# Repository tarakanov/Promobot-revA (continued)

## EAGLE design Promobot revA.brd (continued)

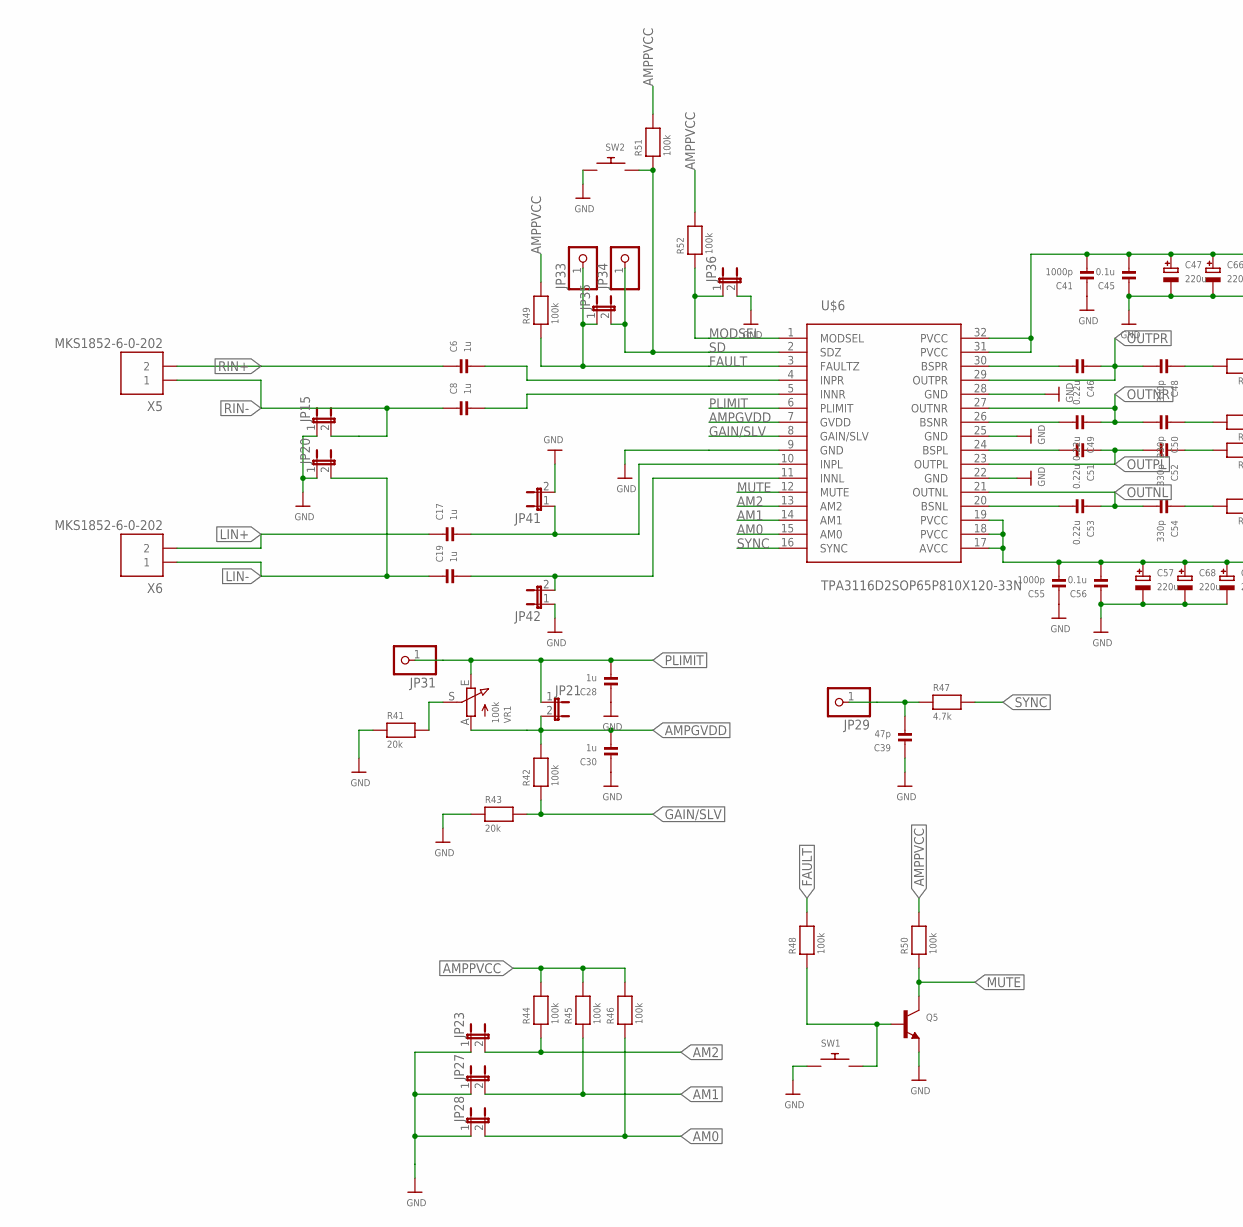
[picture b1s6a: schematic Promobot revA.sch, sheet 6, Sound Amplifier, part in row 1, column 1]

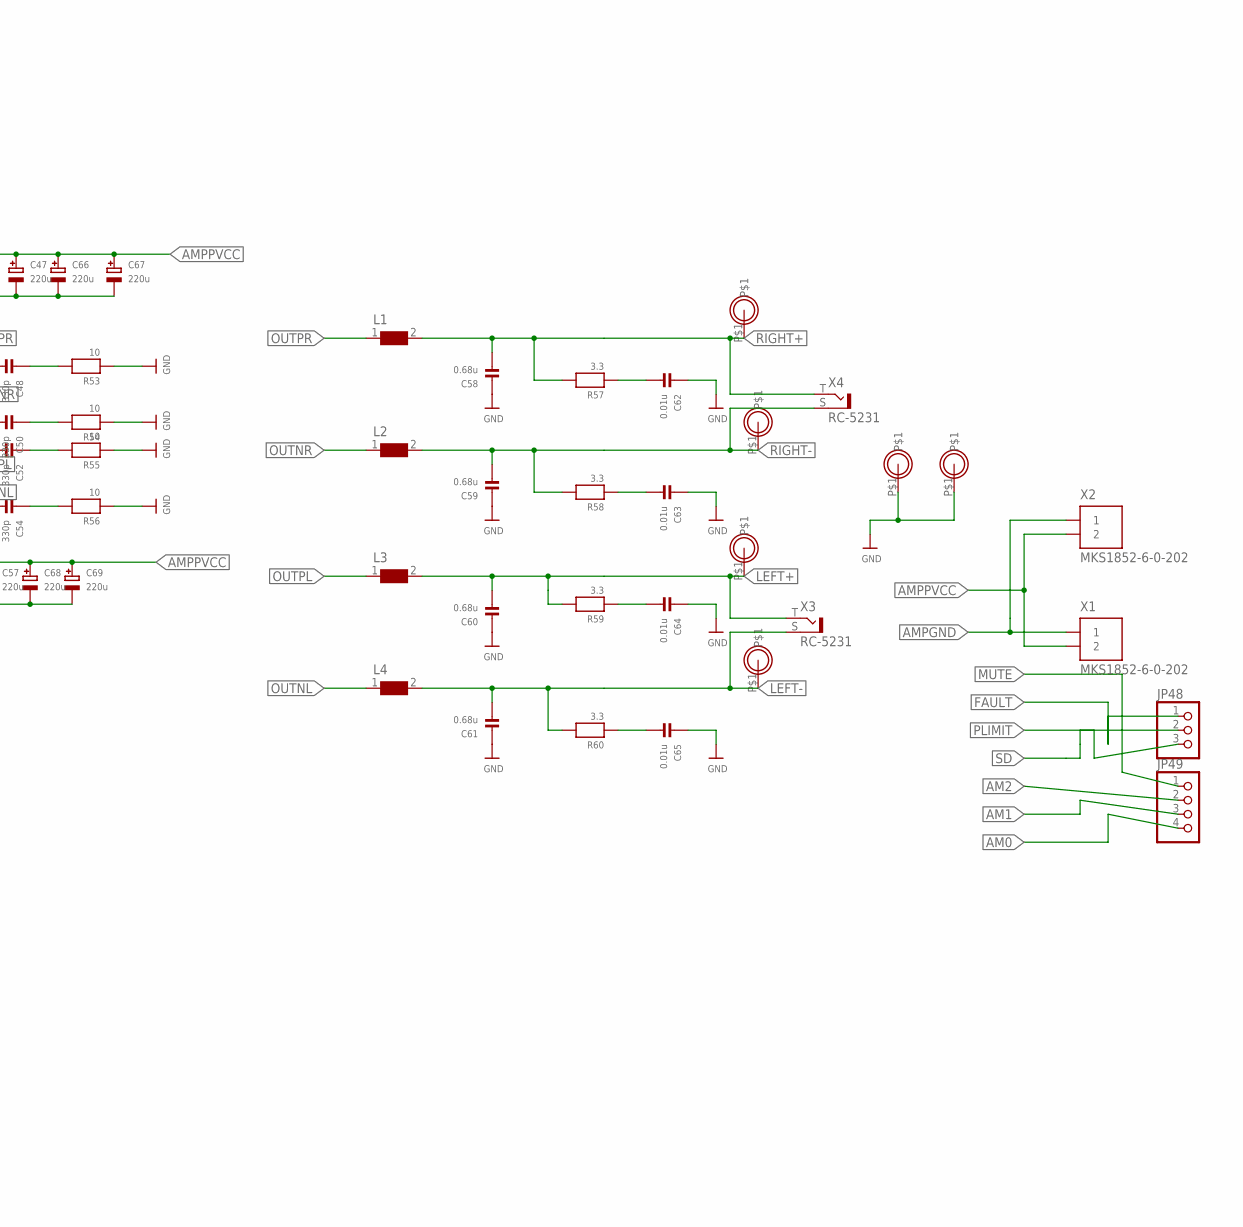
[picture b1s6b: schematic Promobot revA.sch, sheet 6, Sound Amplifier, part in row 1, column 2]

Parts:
C6, C8, C17, C19: 1u; _0603
C28, C30: 1u; _0603MP
C39: 47p; _0603
C41, C55: 1000p; _0603
C45, C56: 0.1u; _0603
C46, C49, C51, C53: 0.22u; _0603
C47, C57, C66, C67, C68, C69: 220u; CELEC_3.5MM_10MM
C48, C50, C52, C54: 330p; _0603
C58, C59, C60, C61: 0.68u; 1206
C62, C63, C64, C65: 0.01u; _0805
JP15, JP20, JP21, JP23, JP27, JP28, JP35, JP36, JP41, JP42: JUMPER2
JP29, JP31, JP33, JP34: HEADER-1X1ROUND; 1X01_ROUND
JP48: HEADER-1X376MIL; 1X03_ROUND_76
JP49: HEADER-1X476MIL; 1X04_ROUND_76
L1, L2, L3, L4: WE-PD-7447709100_1260/1245/1280/1210; WE-PD_1260/1245/1280/1210
Q5: TRANSISTOR_NPNWAVE; SOT23-W
R41: 20k; 0603
R42: 100k; _0805
R43: 20k; _0805
R44, R45, R46, R48, R49, R50, R51, R52: 100k; 0603
R47: 4.7k; 0603
R53, R54, R55, R56: 10; 1206
R57, R58, R59, R60: 3.3; _0603
SW1, SW2: SWITCH_PUSHBUTTONSOFTTOUCHSMD_SJ; PUSHBUTTON_SMD_SJ
U$6: TPA3116D2SOP65P810X120-33N; SOP65P810X120-33N
U$81, U$82, U$83, U$84, U$89, U$90: MOUNTINGHOLE; MOUNTINGHOLE_3.0_PLATED
VR1: 100k; TRIMPOT_BOURNS3MM
X1, X2, X5, X6: MKS1852-6-0-202
X3, X4: RC-5231

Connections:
AM0: JP28.2, JP49.4, R46.1, U$6.15 (AM0)
AM1: JP27.2, JP49.3, R45.1, U$6.14 (AM1)
AM2: JP23.2, JP49.2, R44.1, U$6.13 (AM2)
AMPGND: C28.1, C30.1, C39.1, C41.1, C45.1, C47.-, C55.1, C56.1, C57.-, C58.1, C59.1, C60.1, C61.1, C62.1, C63.1, C64.1, C65.1, C66.-, C67.-, C68.-, C69.-, JP15.1, JP20.1, JP23.1, JP27.1, JP28.1, JP36.2, JP41.2, JP42.1, Q5.2 (E), R41.1, R43.1, R53.1, R54.1, R55.1, R56.1, SW1.P$1, SW2.P$2, U$6.9 (GND), U$6.22 (GND), U$6.25 (GND), U$6.28 (GND), U$89.P$1, U$90.P$1, X1.1, X2.1; also elsewhere on the board
AMPGVDD: C30.2, JP21.2, R42.2, U$6.7 (GVDD), VR1.A
AMPPVCC: C41.2, C45.2, C47.+, C55.2, C56.2, C57.+, C66.+, C67.+, C68.+, C69.+, R44.2, R45.2, R46.2, R49.2, R50.2, R51.2, R52.2, U$6.17 (AVCC), U$6.18 (PVCC), U$6.19 (PVCC), U$6.31 (PVCC), U$6.32 (PVCC), X1.2, X2.2; also elsewhere on the board
FAULT: JP33.1, JP35.1, JP48.1, R48.2, R49.1, U$6.3 (FAULTZ)
GAIN/SLV: R42.1, R43.2, U$6.8 (GAIN/SLV)
LEFT+: C60.2, L3.2, R59.2, U$83.P$1, X3.T
LEFT-: C61.2, L4.2, R60.2, U$84.P$1, X3.S
LIN+: C17.1, X6.2
LIN-: C19.1, JP20.2, X6.1
MODSEL: JP36.1, R52.1, U$6.1 (MODSEL)
MUTE: JP49.1, Q5.3 (C), R50.1, U$6.12 (MUTE)
unnamed: R41.2, VR1.S
unnamed: C39.2, JP29.1, R47.1
unnamed: Q5.1 (B), R48.1, SW1.P$2
unnamed: C6.2, U$6.4 (INPR)
unnamed: C8.2, U$6.5 (INNR)
unnamed: C46.2, U$6.30 (BSPR)
unnamed: C48.1, R53.2
unnamed: C17.2, JP41.1, U$6.10 (INPL)
unnamed: C19.2, JP42.2, U$6.11 (INNL)
unnamed: C51.2, U$6.24 (BSPL)
unnamed: C49.2, U$6.26 (BSNR)
unnamed: C50.1, R54.2
unnamed: C65.2, R60.1
unnamed: C52.1, R55.2
unnamed: C62.2, R57.1
unnamed: C53.2, U$6.20 (BSNL)
unnamed: C63.2, R58.1
unnamed: C54.1, R56.2
unnamed: C64.2, R59.1
OUTNL: C53.1, C54.2, L4.1, U$6.21 (OUTNL)
OUTNR: C49.1, C50.2, L2.1, U$6.27 (OUTNR)
OUTPL: C51.1, C52.2, L3.1, U$6.23 (OUTPL)
OUTPR: C46.1, C48.2, L1.1, U$6.29 (OUTPR)
PLIMIT: C28.2, JP21.1, JP31.1, JP48.3, U$6.6 (PLIMIT), VR1.E
RIGHT+: C58.2, L1.2, R57.2, U$81.P$1, X4.T
RIGHT-: C59.2, L2.2, R58.2, U$82.P$1, X4.S
RIN+: C6.1, X5.2
RIN-: C8.1, JP15.2, X5.1
SD: JP34.1, JP35.2, JP48.2, R51.1, SW2.P$1, U$6.2 (SDZ)
SYNC: R47.2, U$6.16 (SYNC)

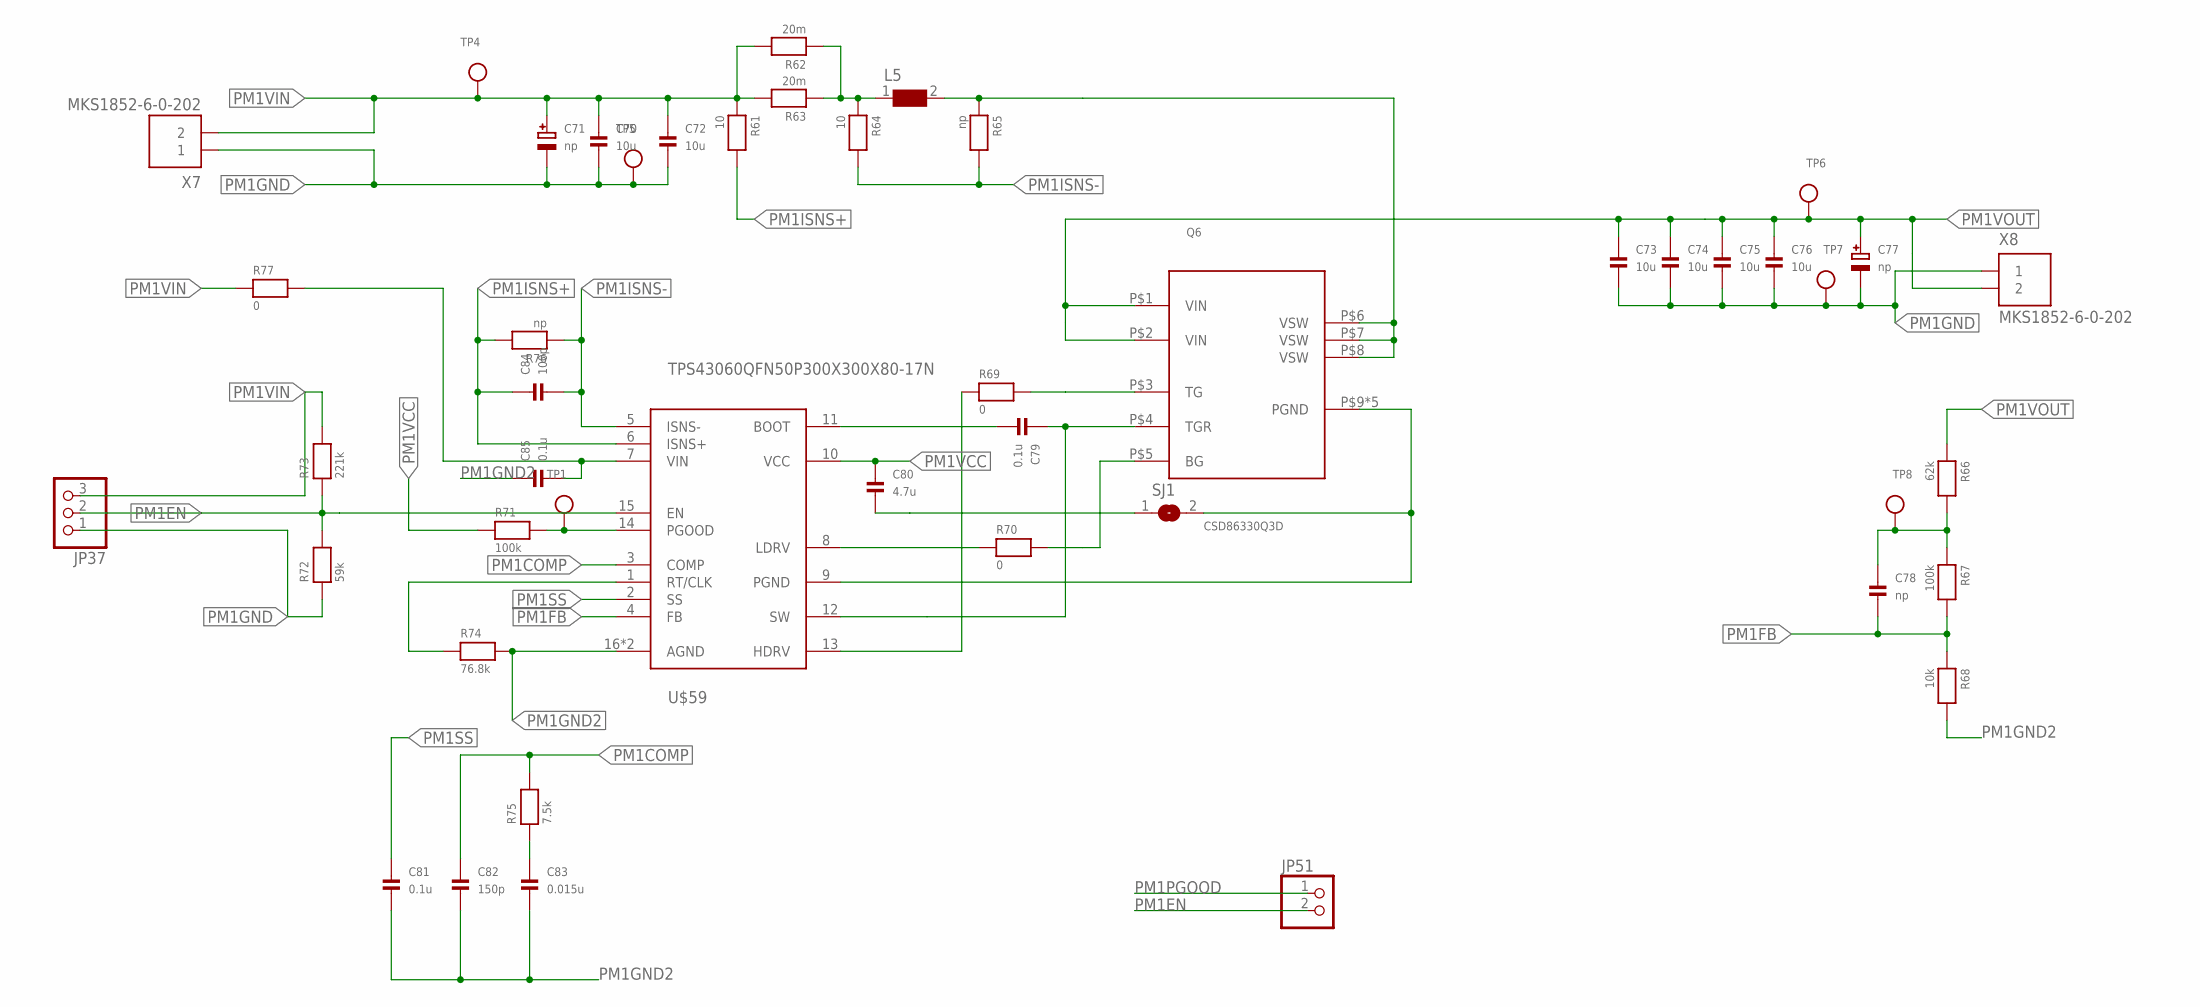
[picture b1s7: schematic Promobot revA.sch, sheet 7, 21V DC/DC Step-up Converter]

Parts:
C70, C72, C73, C74, C75, C76: 10u; 1206
C71, C77: np; CELEC_3.5MM_10MM
C78: np; _0603
C79, C81: 0.1u; _0603
C80: 4.7u; _0603
C82: 150p; _0603
C83: 0.015u; _0603
C84: 100p; _0603MP
C85: 0.1u; _0603MP
JP37: HEADER-1X376MIL; 1X03_ROUND_76
JP51: HEADER-1X2ROUND; 1X02_ROUND
L5: WE-HCI-744311330_7030/7040/7050; WE-HCI_7030/7040/7050
Q6: CSD86330Q3D; SON330X330
R61, R64: 10; _0603MP
R62, R63: 20m; 1206
R65, R76: np; _0603MP
R66: 62k; 0603
R67, R71: 100k; 0603
R68: 10k; 0603
R69, R70, R77: 0; 0603
R72: 59k; 0603
R73: 221k; 0603
R74: 76.8k; 0603
R75: 7.5k; 0603
SJ1: SOLDERJUMPER; SOLDERJUMPER_ARROW_NOPASTE
TP1, TP4, TP5, TP6, TP7, TP8: TESTPOINT0.1"; 1X01_ROUND
U$59: TPS43060QFN50P300X300X80-17N; QFN50P300X300X80-17N
X7, X8: MKS1852-6-0-202

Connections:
unnamed: L5.1, R62.1, R63.1, R64.1
unnamed: L5.2, Q6.P$6 (VSW), Q6.P$7 (VSW), Q6.P$8 (VSW), R65.1
unnamed: C78.1, R66.2, R67.1, TP8.1
unnamed: Q6.P$3 (TG), R69.2
unnamed: R69.1, U$59.13 (HDRV)
unnamed: C79.1, Q6.P$4 (TGR), U$59.12 (SW)
unnamed: C79.2, U$59.11 (BOOT)
unnamed: R70.1, U$59.8 (LDRV)
unnamed: Q6.P$5 (BG), R70.2
unnamed: R74.1, U$59.1 (RT/CLK)
unnamed: C83.1, R75.1
unnamed: C85.2, R77.2, U$59.7 (VIN)
PM1COMP: C82.1, R75.2, U$59.3 (COMP)
PM1EN: JP37.2, JP51.2, R72.2, R73.1, U$59.15 (EN)
PM1FB: C78.2, R67.2, R68.1, U$59.4 (FB)
PM1GND: C70.2, C71.-, C72.2, C73.2, C74.2, C75.2, C76.2, C77.-, JP37.1, Q6.P$9 (PGND), Q6.P$10 (PGND), Q6.P$11 (PGND), Q6.P$12 (PGND), Q6.P$13 (PGND), R72.1, SJ1.2, TP5.1, TP7.1, U$59.9 (PGND), X7.1, X8.1; also elsewhere on the board
PM1GND2: C80.2, C81.2, C82.2, C83.2, C85.1, R68.2, R74.2, SJ1.1, U$59.16 (AGND), U$59.17 (AGND)
PM1ISNS+: C84.1, R61.2, R76.2, U$59.6 (ISNS+)
PM1ISNS-: C84.2, R64.2, R65.2, R76.1, U$59.5 (ISNS-)
PM1PGOOD: JP51.1, R71.2, TP1.1, U$59.14 (PGOOD)
PM1SS: C81.1, U$59.2 (SS)
PM1VCC: C80.1, R71.1, U$59.10 (VCC)
PM1VIN: C70.1, C71.+, C72.1, JP37.3, R61.1, R62.2, R63.2, R73.2, R77.1, TP4.1, X7.2; also elsewhere on the board
PM1VOUT: C73.1, C74.1, C75.1, C76.1, C77.+, Q6.P$1 (VIN), Q6.P$2 (VIN), R66.1, TP6.1, X8.2; also elsewhere on the board

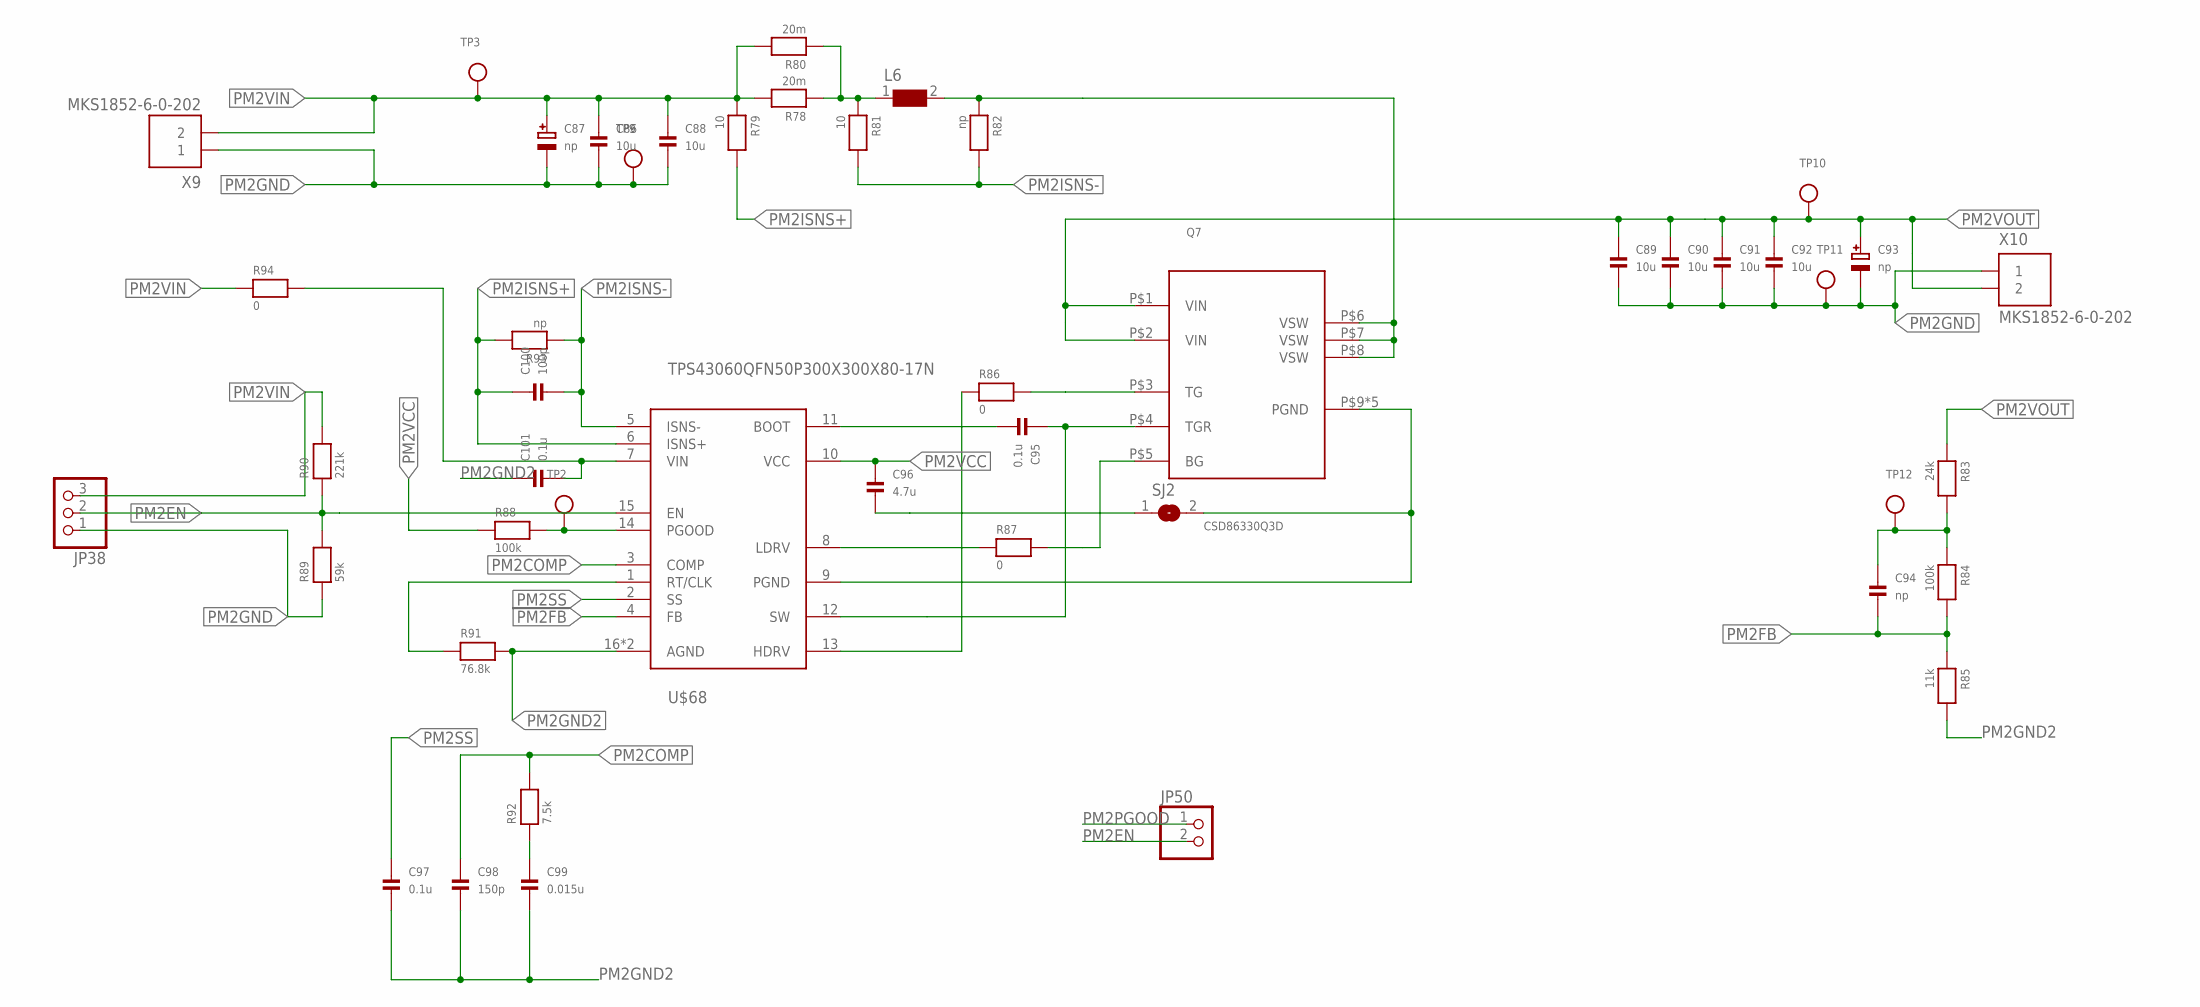
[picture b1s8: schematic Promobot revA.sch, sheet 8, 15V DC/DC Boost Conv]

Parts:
C86, C88, C89, C90, C91, C92: 10u; 1206
C87, C93: np; CELEC_3.5MM_10MM
C94: np; _0603
C95, C97: 0.1u; _0603
C96: 4.7u; _0603
C98: 150p; _0603
C99: 0.015u; _0603
C100: 100p; _0603MP
C101: 0.1u; _0603MP
JP38: HEADER-1X376MIL; 1X03_ROUND_76
JP50: HEADER-1X2ROUND; 1X02_ROUND
L6: WE-HCI-744311330_7030/7040/7050; WE-HCI_7030/7040/7050
Q7: CSD86330Q3D; SON330X330
R78, R80: 20m; 1206
R79, R81: 10; _0603MP
R82, R93: np; _0603MP
R83: 24k; 0603
R84, R88: 100k; 0603
R85: 11k; 0603
R86, R87, R94: 0; 0603
R89: 59k; 0603
R90: 221k; 0603
R91: 76.8k; 0603
R92: 7.5k; 0603
SJ2: SOLDERJUMPER; SOLDERJUMPER_ARROW_NOPASTE
TP2, TP3, TP9, TP10, TP11, TP12: TESTPOINT0.1"; 1X01_ROUND
U$68: TPS43060QFN50P300X300X80-17N; QFN50P300X300X80-17N
X9, X10: MKS1852-6-0-202

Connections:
unnamed: L6.1, R78.1, R80.1, R81.1
unnamed: L6.2, Q7.P$6 (VSW), Q7.P$7 (VSW), Q7.P$8 (VSW), R82.1
unnamed: C94.1, R83.2, R84.1, TP12.1
unnamed: Q7.P$3 (TG), R86.2
unnamed: R86.1, U$68.13 (HDRV)
unnamed: C95.1, Q7.P$4 (TGR), U$68.12 (SW)
unnamed: C95.2, U$68.11 (BOOT)
unnamed: R87.1, U$68.8 (LDRV)
unnamed: Q7.P$5 (BG), R87.2
unnamed: R91.1, U$68.1 (RT/CLK)
unnamed: C99.1, R92.1
unnamed: C101.2, R94.2, U$68.7 (VIN)
PM2COMP: C98.1, R92.2, U$68.3 (COMP)
PM2EN: JP38.2, JP50.2, R89.2, R90.1, U$68.15 (EN)
PM2FB: C94.2, R84.2, R85.1, U$68.4 (FB)
PM2GND: C86.2, C87.-, C88.2, C89.2, C90.2, C91.2, C92.2, C93.-, JP38.1, Q7.P$9 (PGND), Q7.P$10 (PGND), Q7.P$11 (PGND), Q7.P$12 (PGND), Q7.P$13 (PGND), R89.1, SJ2.2, TP9.1, TP11.1, U$68.9 (PGND), X9.1, X10.1
PM2GND2: C96.2, C97.2, C98.2, C99.2, C101.1, R85.2, R91.2, SJ2.1, U$68.16 (AGND), U$68.17 (AGND)
PM2ISNS+: C100.1, R79.2, R93.2, U$68.6 (ISNS+)
PM2ISNS-: C100.2, R81.2, R82.2, R93.1, U$68.5 (ISNS-)
PM2PGOOD: JP50.1, R88.2, TP2.1, U$68.14 (PGOOD)
PM2SS: C97.1, U$68.2 (SS)
PM2VCC: C96.1, R88.1, U$68.10 (VCC)
PM2VIN: C86.1, C87.+, C88.1, JP38.3, R78.2, R79.1, R80.2, R90.2, R94.1, TP3.1, X9.2
PM2VOUT: C89.1, C90.1, C91.1, C92.1, C93.+, Q7.P$1 (VIN), Q7.P$2 (VIN), R83.1, TP10.1, X10.2

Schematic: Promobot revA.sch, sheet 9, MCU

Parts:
C102, C104, C106, C108, C109, C110: 100n; _0603
C103, C111, C112: 1u; _0603
C105, C107: 22u; EIA3216-18/A-R
C113: 22P; _0603
C114: 22p; _0603
D2: CD1206-S01575; MINIMELF
F1: MF-MSMF050-2 500mA; L1812
J3: USB-MICRO!!!; CON2_USB_MICRO_B_AT
J4: 3x2M; 2X03
JP58: HEADER-1X15; 1X15_ROUND_70
JP59, JP60: HEADER-1X1070MIL; 1X10_ROUND70
JP61: HEADER-1X2ROUND; 1X02_ROUND
L8: MH2029-300Y; 0805
L9: green; CHIPLED_0603
ON: blue; CHIPLED_0603
R95, R100, R103, R104: 10k; _0603
R96, R97, R98, R99, R108, R109: 1k; _0603
R101, R102: 22; _0603
R110: 3k; _0603MP
R111: 1k; _0603MP
RESET: TS42
RX: yellow; CHIPLED_0603
T1: FDN340P/PMV48XP; SOT-23
T2: PMV48XP; SOT-23
TX: yellow; CHIPLED_0603
U9: LP2985-33DBVR; SOT23-DBV
U10: ATMEGA32U4-XUMU; QFN44ML7X7
U11: NCP1117-5; LINEAR_SOT223
X19, X20, X21: MKS1852-6-0-202
Y3: 16MHz KX-7; CRYSTAL-3.2-2.5
Z1, Z2: CG0603MLC-05E; CT/CN0603

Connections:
3V3: C103.1, U9.5 (OUT)
5-GND: RESET.5 (5-GND)
+5V: C104.1, C105.+, C109.1, C110.1, D2.C, J4.2, L8.1, R96.1, R100.2, R108.2, R109.2, T1.2 (S), T2.3 (G), U9.1 (IN), U9.3 (ON/!OFF), U10.2 (UVCC), U10.14 (VCC), U10.24 (AVCC), U10.34 (VCC1), U11.2 (OUT), U11.4 (OUT)
+VIN: C106.1, T2.2 (S), U11.3 (IN)
A0: JP60.1, U10.36 ((ADC7/TDI)PF7)
A1: R110.1, R111.1, U10.37 ((ADC6/TDO)PF6)
A2: JP60.8, U10.38 ((ADC5/TMS)PF5)
A3: JP60.3, U10.39 ((ADC4/TCK)PF4)
A4: JP59.8, U10.40 ((ADC1)PF1)
A5: JP59.3, U10.41 ((ADC0)PF0)
AREF: C108.1, JP61.2, U10.42 (AREF)
AVCC: C112.1, L8.2, U10.44 (AVCC1)
D0/RX: JP59.10, U10.20 ((RXD1/AIN1/INT2)PD2)
D1/TX: JP59.6, U10.21 ((TXD1/INT3)PD3)
D2/SDA: R108.1, U10.19 ((SDA/INT1)PD1), X19.1, X20.1, X21.1
D3/SCL: R109.1, U10.18 ((OC0B/SCL/INT0)PD0), X19.2, X20.2, X21.2
D4*: JP59.5, U10.25 ((ICP1/ADC8)PD4)
D5*: JP59.7, U10.31 ((OC3A/#0C4A)PC6)
D6*: JP60.2, U10.27 ((T0/OC4D/ADC10)PD7)
D7: JP59.1, U10.1 ((INT6/AIN0)PE6)
D+: J3.P3 (D+), R101.2, Z1.1
D-: J3.P2 (D-), R102.2, Z2.1
GND: C102.2, C103.2, C104.2, C105.-, C106.2, C107.-, C108.2, C109.2, C110.2, C111.2, C112.2, C113.1, C114.1, J3.P5 (GND), J3.S1 (SH1), J3.S2 (SH2), J3.S3 (SH3), J3.S4 (SH4), J3.S5 (SH5), J3.S6 (SH6), J4.6, JP61.1, L9.C, ON.C, R95.2, R103.1, R104.1, R111.2, RESET.3, RESET.4, RX.C, TX.C, U9.2 (GND), U10.5 (UGND), U10.15 (GND), U10.23 (GND1), U10.35 (GND2), U10.43 (GND3), U10.EXP (PAD), U11.1 (GND/ADJ), Y3.2 (GND), Y3.4 (GND), Z1.2, Z2.2
HWB: R95.1, U10.33 ((#HWB)PE2)
IO8: JP58.7, U10.28 ((ADC11/PCINT4)PB4)
IO9*: JP60.7, U10.29 ((PCINT5/OC1A/#OC4B/ADC12)PB5)
IO10*: JP58.1, U10.30 ((PCINT6/OC1B/OC4B/ADC13)PB6)
IO11*: JP58.2, U10.12 ((PCINT7/OC0A/OC1C/#RTS)PB7)
IO12*: JP58.6, U10.26 ((T1/#OC4D/ADC9)PD6)
IO13*: JP59.2, R99.1, U10.32 ((ICP3/CLK0/OC4A)PC7)
MISO: J4.1, JP60.10, U10.11 ((PD0/MISO/PCINT3)PB3)
MOSI: J4.4, JP60.6, U10.10 ((PDI/MOSI/PCINT2)PB2)
unnamed: L9.A, R99.2
unnamed: R98.2, RX.A
unnamed: R97.2, TX.A
unnamed: ON.A, R96.2
RD+: R101.1, U10.4 (D+)
RD-: R102.1, U10.3 (D-)
RESET: D2.A, J4.5, R100.1, RESET.1, RESET.2, U10.13 (RESET)
RXLED/SS: JP58.3, JP58.12, JP58.13, JP59.4, JP59.9, JP60.4, JP60.9, R98.1, U10.8 ((SS/PCINT0)PB0)
SCK: J4.3, JP60.5, U10.9 ((SCLK/PCINT1)PB1)
TXLED: JP58.5, R97.1, U10.22 ((XCK1/#CTS)PD5)
UCAP: C111.1, U10.6 (UCAP)
VBAT: JP58.4, R110.2
VIN: R104.2, T1.3 (G), T2.1 (D)
VUSB: C102.1, F1.2, R103.2, T1.1 (D), U10.7 (VBUS)
VUSBD: C107.+, F1.1, J3.P1 (VBUS)
XTAL1: C113.2, U10.17 (XTAL1), Y3.3 (C2)
XTAL2: C114.2, U10.16 (XTAL2), Y3.1 (C1)

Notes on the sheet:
+5V REG
ICSP
USB
+5V SELECTOR (USB)
+3V3 REG
#PWM 8bit
#PWM Hi-Speed
#PWM 16bit
#PWM 10bit
#PWM 8/16bit
Vlotage divider

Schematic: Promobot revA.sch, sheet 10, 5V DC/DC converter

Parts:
C115, C118: 0.1u; _0603
C116, C117: 10u; 1206
C119, C120, C121: 22u; 1206
JP44, JP45: HEADER-1X376MIL; 1X03_ROUND_76
JP57: HEADER-1X2ROUND; 1X02_ROUND
L7: WE-HCI-744311330_7030/7040/7050; WE-HCI_7030/7040/7050
R105, R107: 10k; _0603
R106: 54.9k; _0603
U12: TPS563200; SOT95P280X145-6N

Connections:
unnamed: R105.1, U12.5 (EN)
unnamed: R106.2, R107.1, U12.4 (VFB)
unnamed: C118.1, L7.1, U12.2 (SW)
unnamed: C118.2, U12.6 (VBST)
PM3EN: R105.2; also elsewhere on the board
PM3GND: C115.2, C116.2, C117.2, C119.2, C120.2, C121.2, JP44.1, JP45.1, JP57.1, R107.2, U12.1 (GND); also elsewhere on the board
PM3VIN: C115.1, C116.1, C117.1, JP57.2, U12.3 (VIN); also elsewhere on the board
PM3VOUT: C119.1, C120.1, C121.1, JP44.2, JP45.2, L7.2, R106.1
PPM1: JP44.3; also elsewhere on the board
PPM2: JP45.3; also elsewhere on the board

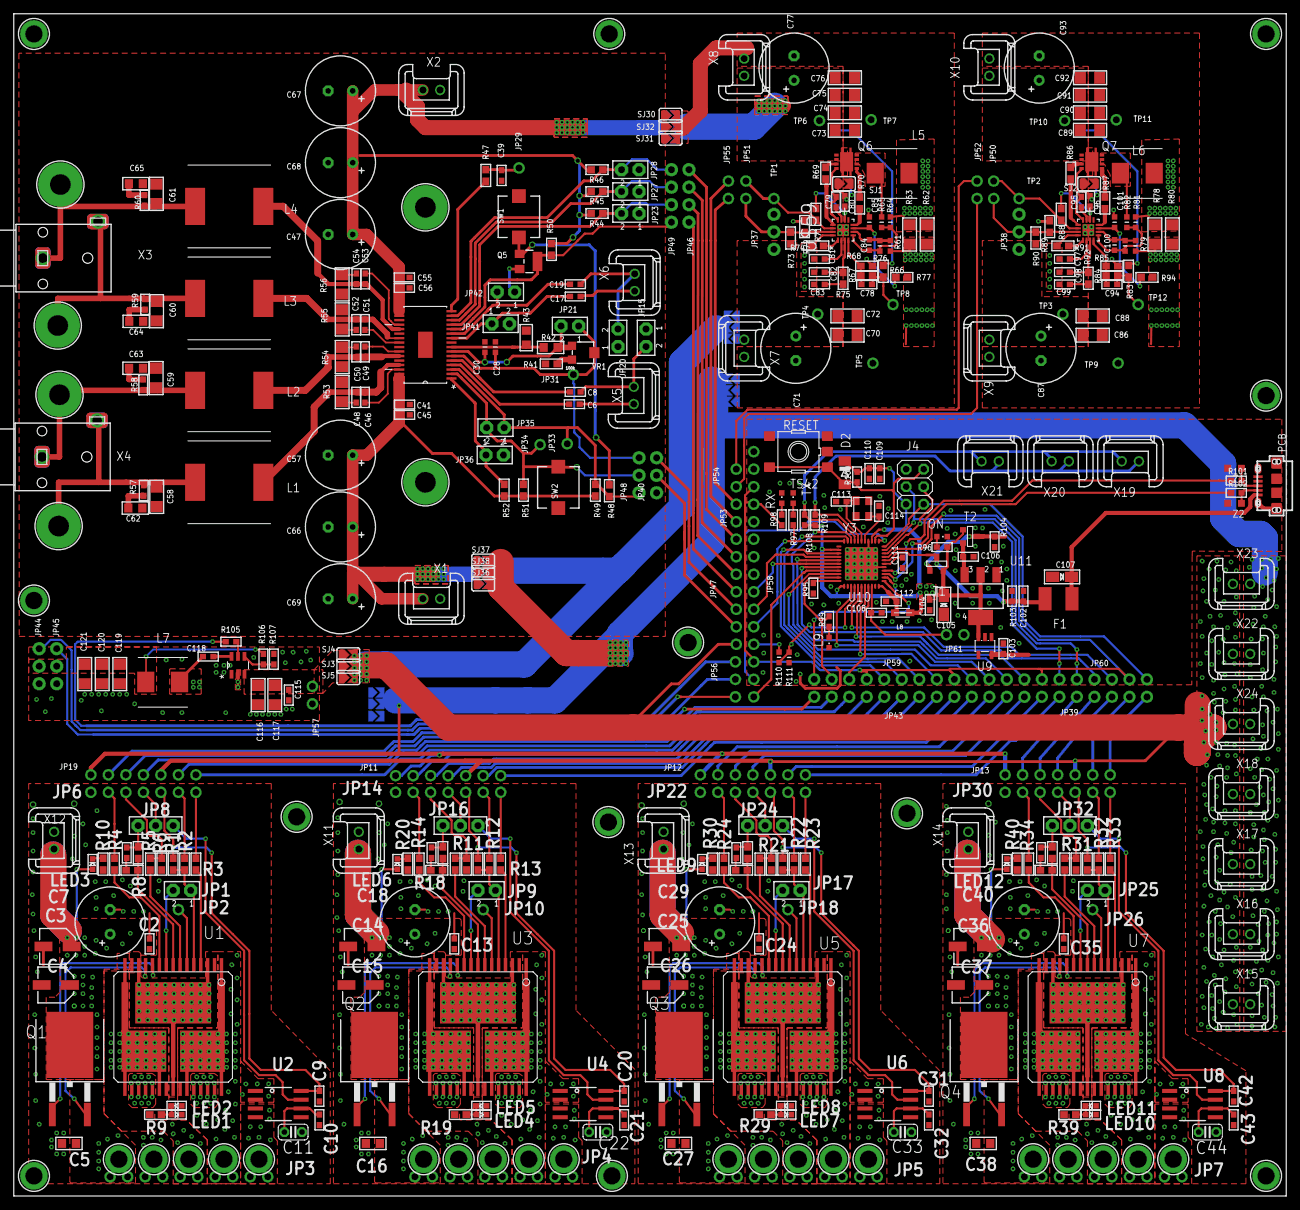
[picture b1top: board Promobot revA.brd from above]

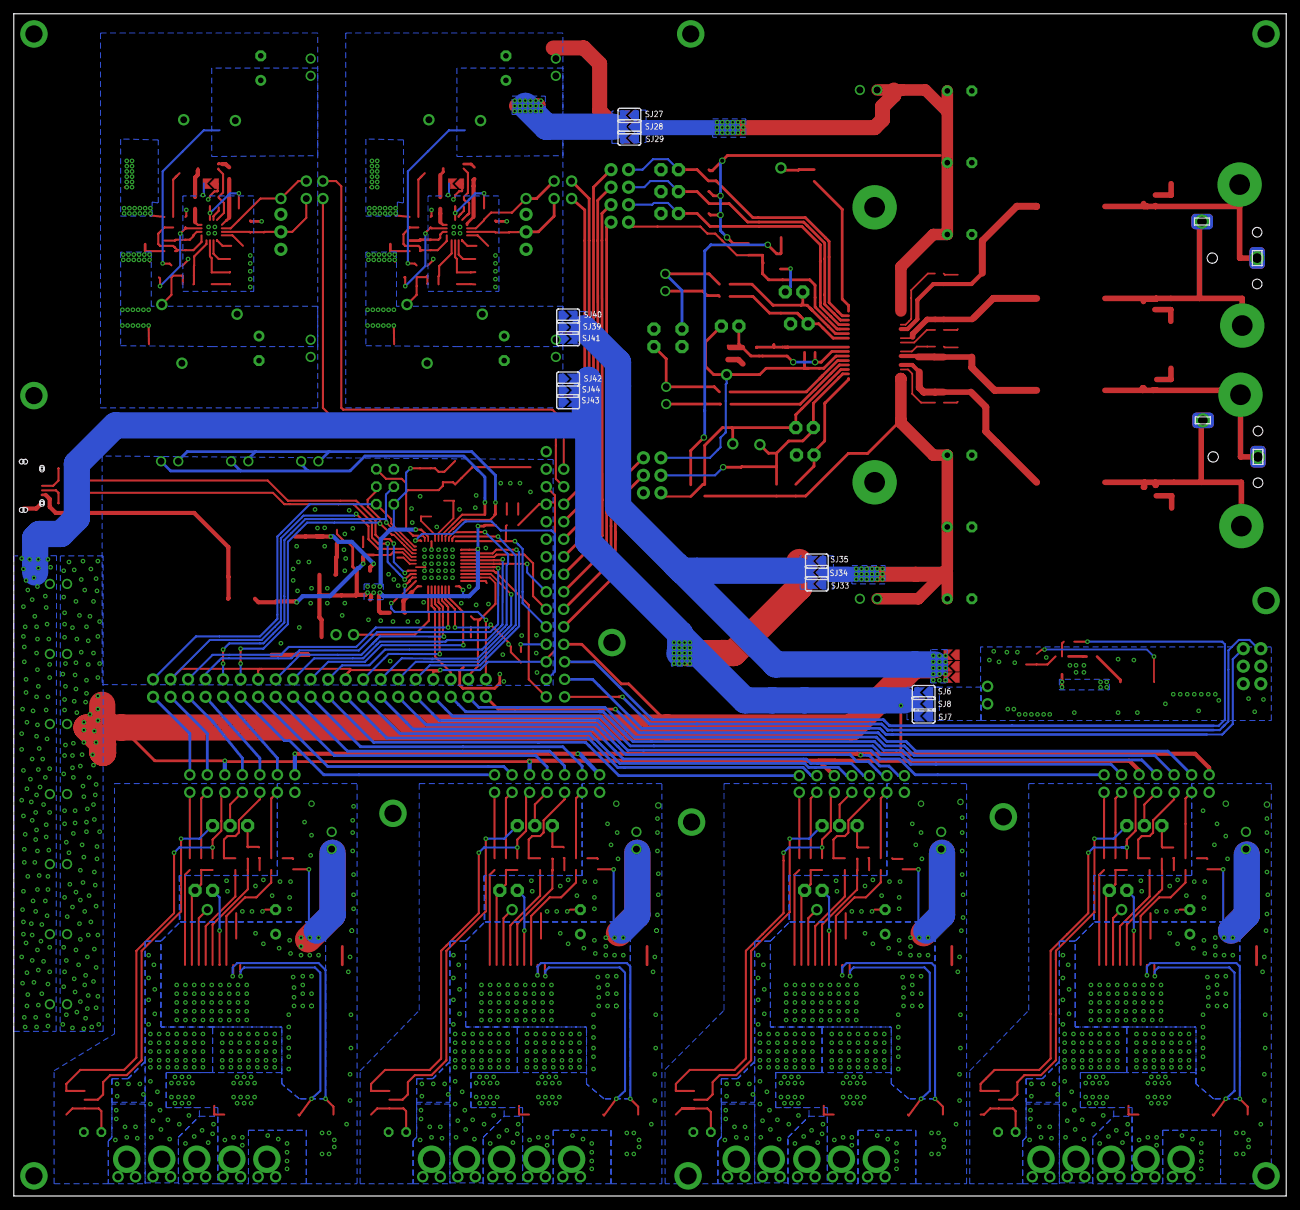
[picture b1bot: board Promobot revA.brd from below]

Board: 2 copper layers, 184.5 x 171.4 mm, 452 parts (15 on the bottom side), 282 nets.

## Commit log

2014-12-31 Update README.md
    Add some info and license
2014-12-31 Add Eagle files
    add .sch and .brd files
2015-01-14 Add voltage divider
    R110, R111 - voltage divider. Connected to A5 pin
